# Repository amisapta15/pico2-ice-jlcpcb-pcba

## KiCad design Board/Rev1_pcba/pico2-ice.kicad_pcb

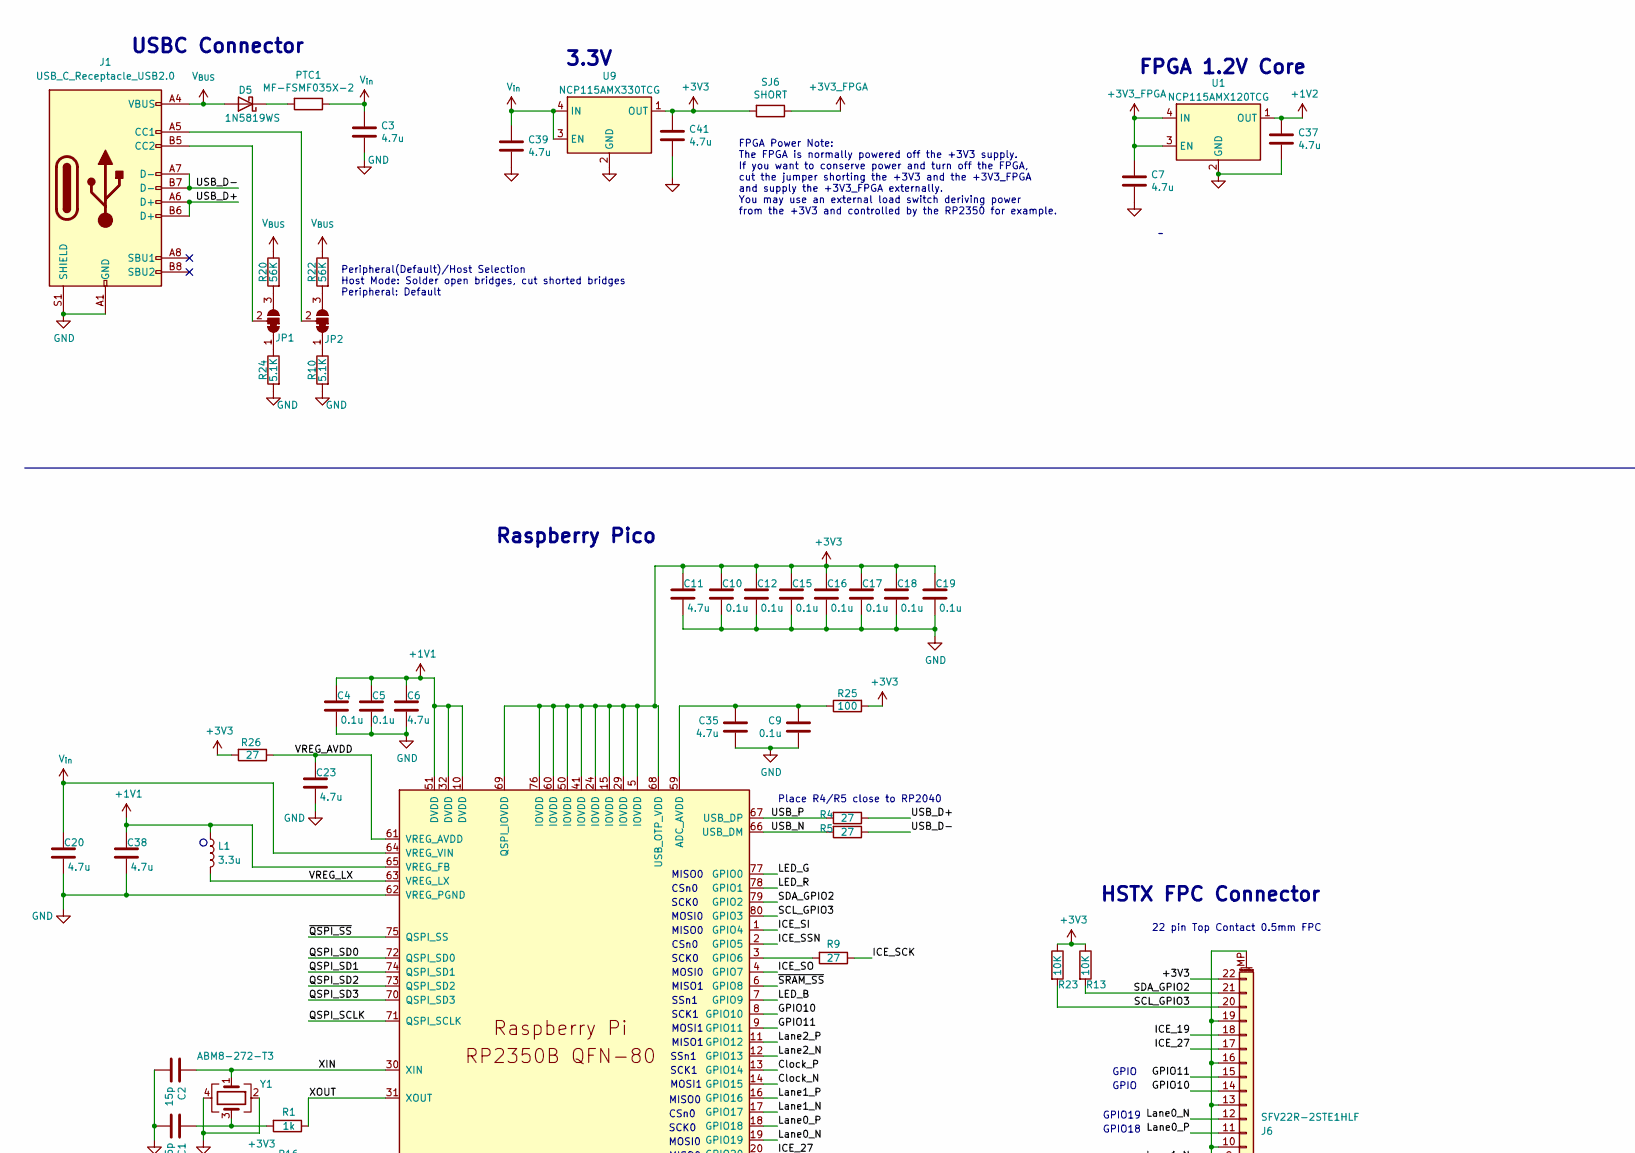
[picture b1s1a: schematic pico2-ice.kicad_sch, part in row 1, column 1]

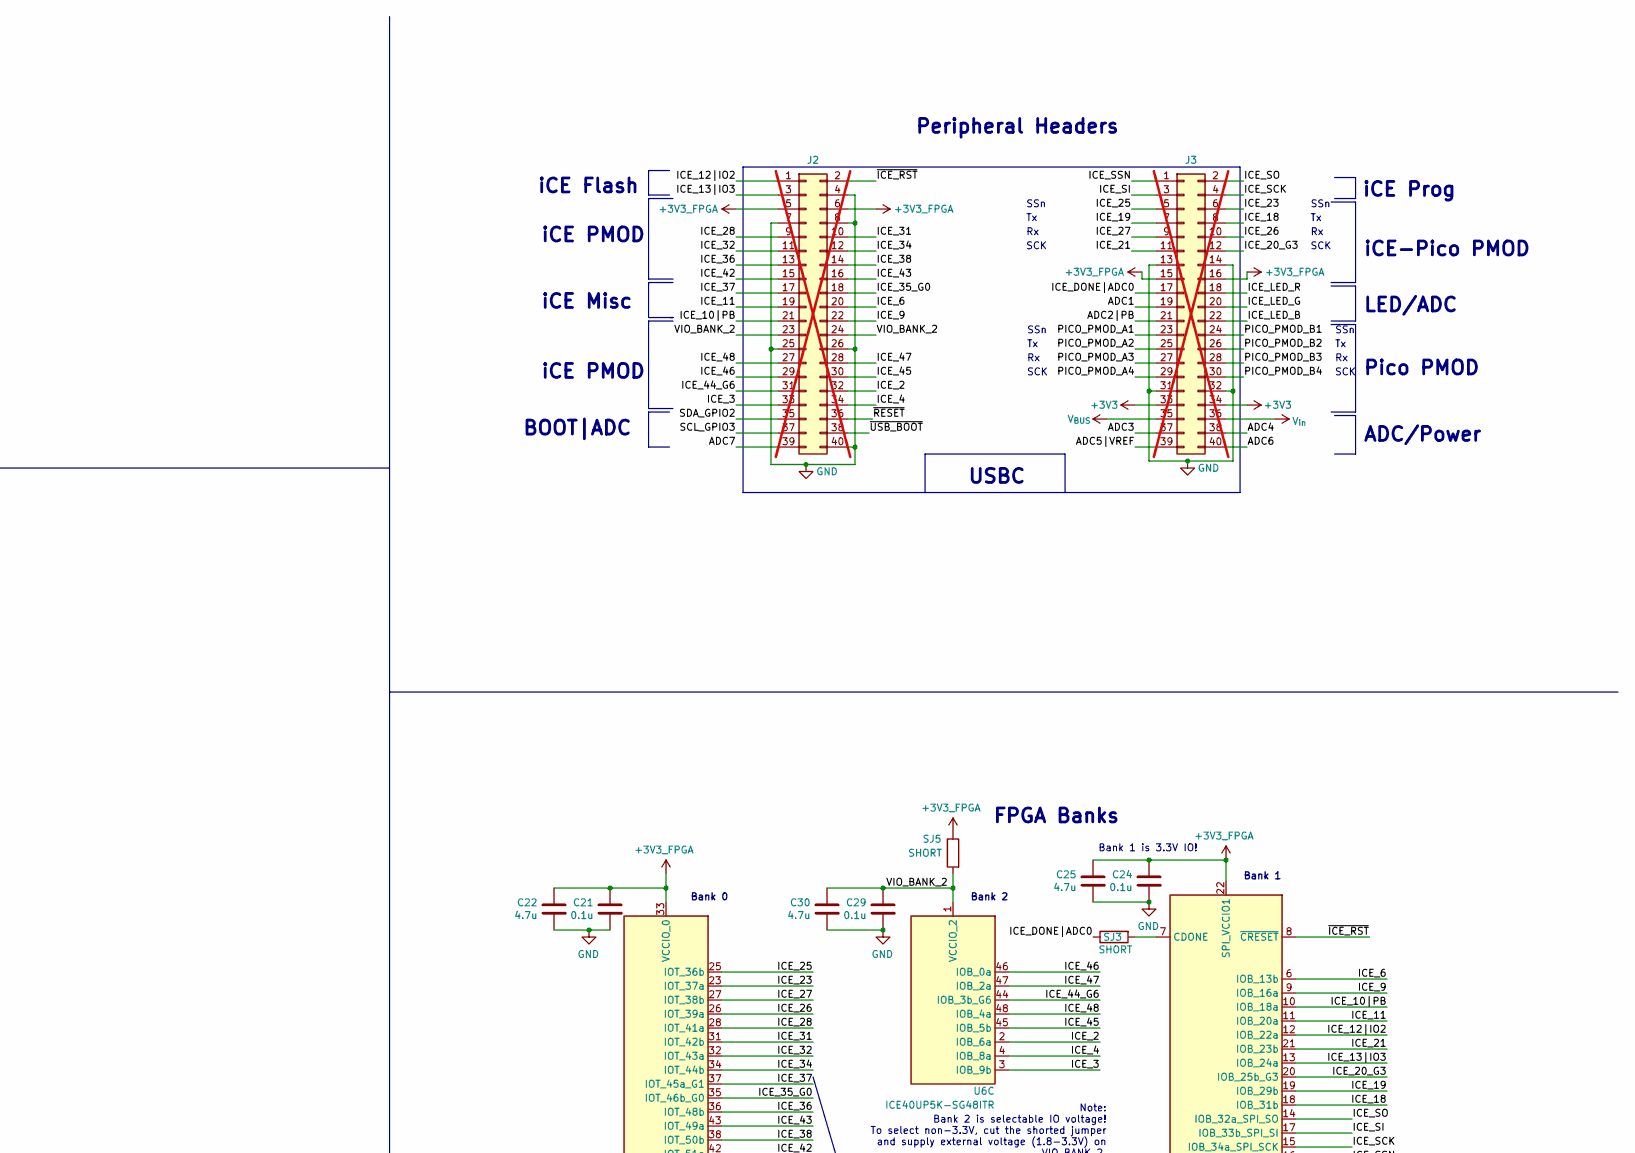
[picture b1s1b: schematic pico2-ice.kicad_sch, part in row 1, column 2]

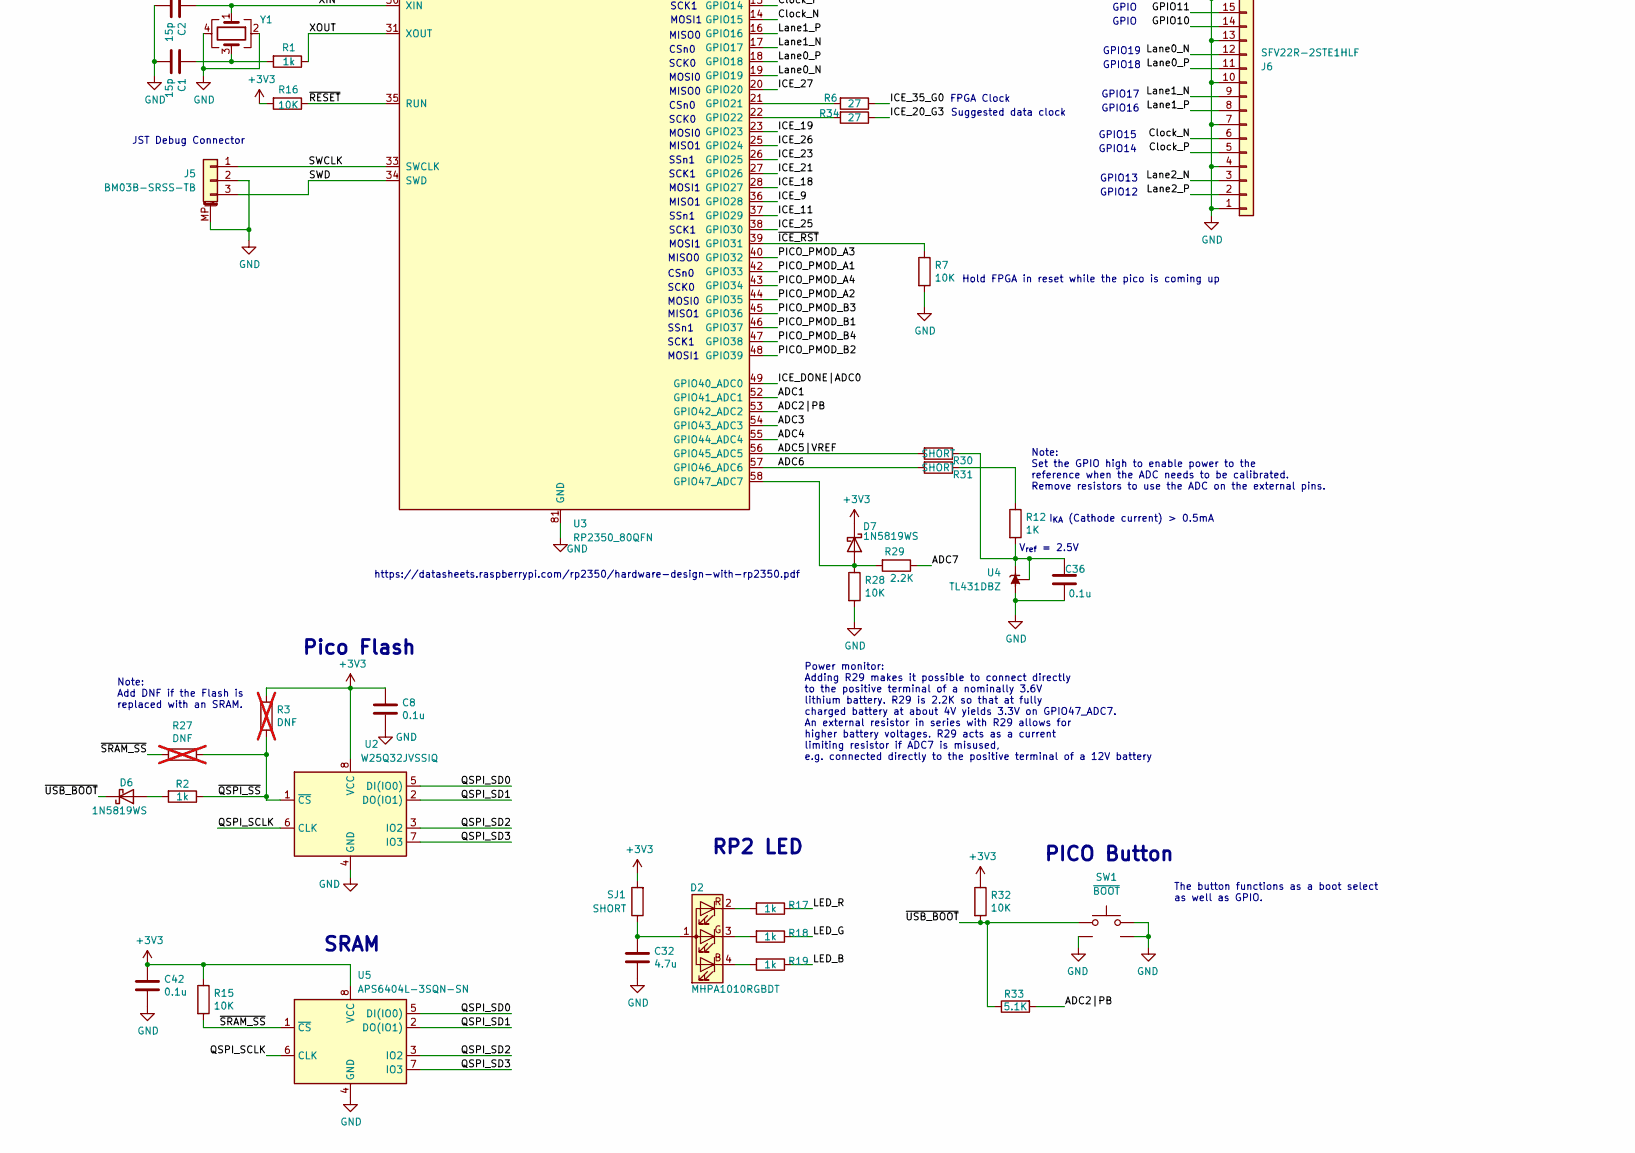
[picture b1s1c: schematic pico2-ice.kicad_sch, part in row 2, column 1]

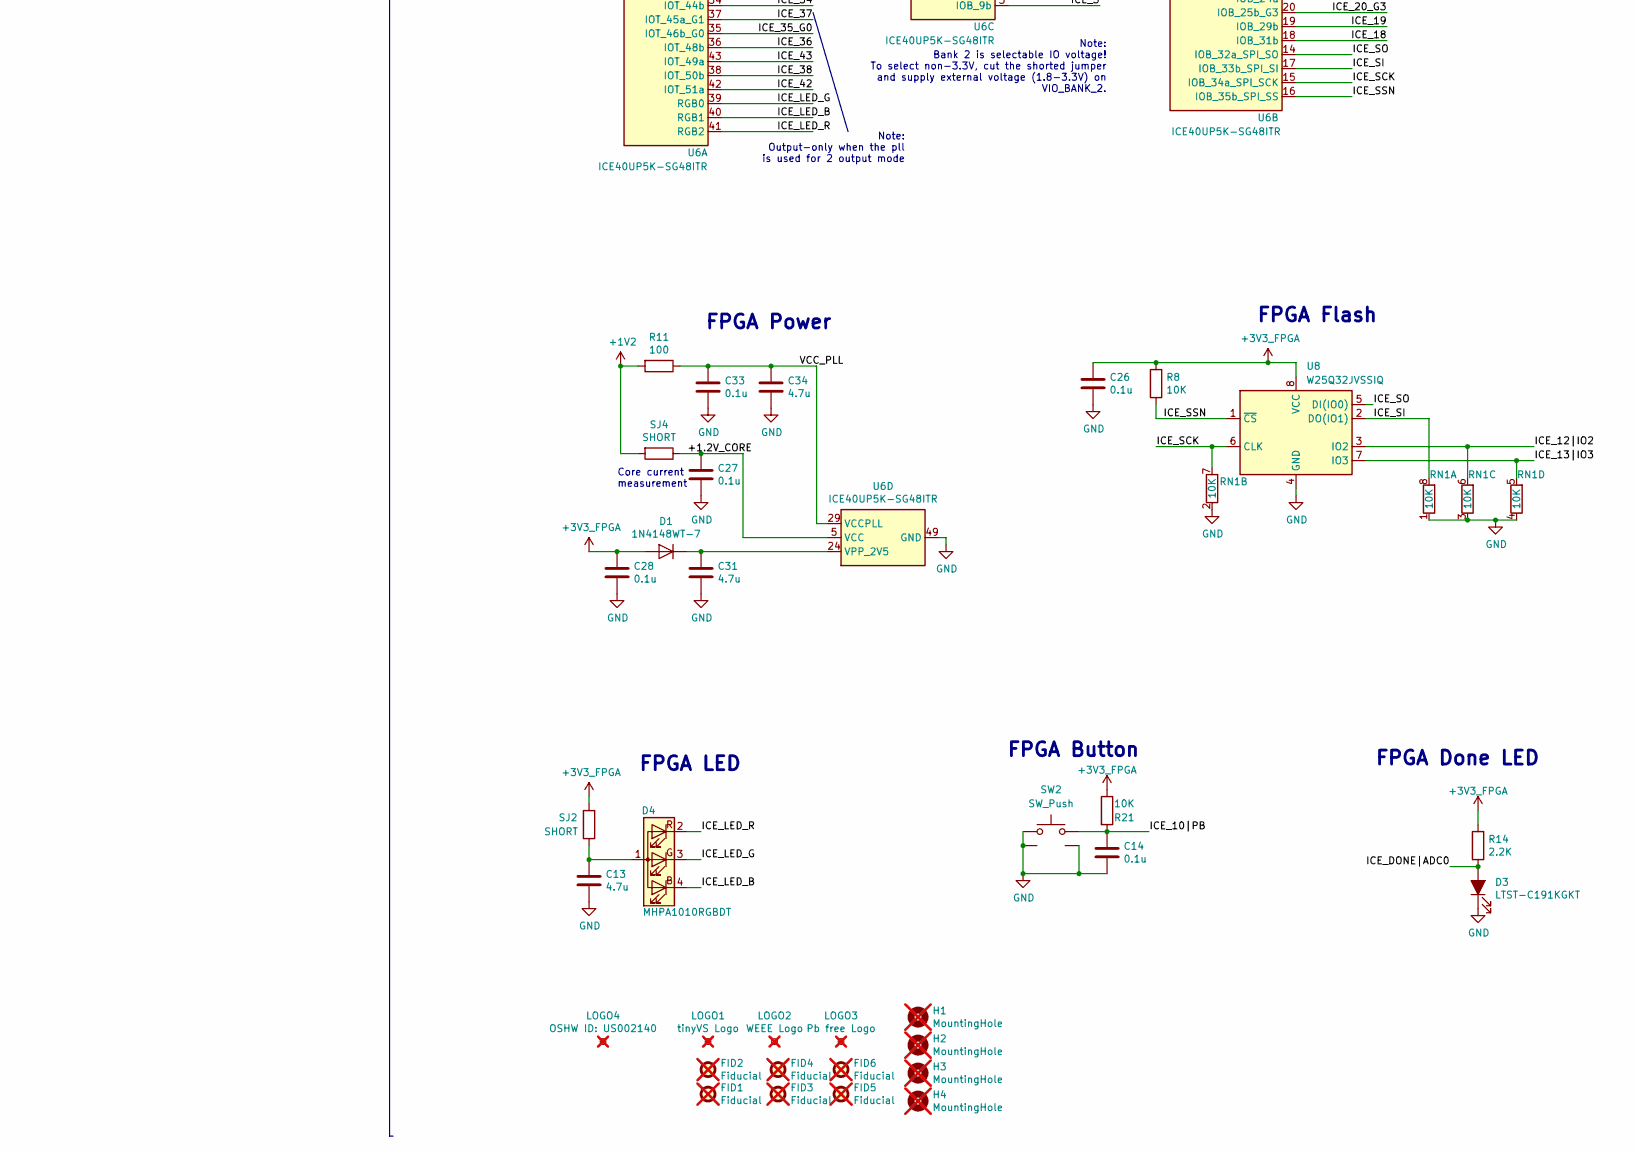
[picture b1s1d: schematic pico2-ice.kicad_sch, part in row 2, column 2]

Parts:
C1, C2: 15p; C_0402_1005Metric; MPN GRM1555C1E150JA01D
C3, C6, C7, C11, C13, C20, C22, C23, C25, C30, C31, C32, C34, C35, C37, C38, C39, C41: 4.7u; C_0402_1005Metric; MPN GRM155R60J475ME87D
C4, C5, C8, C9, C10, C12, C14, C15, C16, C17, C18, C19, C21, C24, C26, C27, C28, C29, C33, C36, C42: 0.1u; C_0402_1005Metric; MPN GRM155R71C104KA88J
D1: 1N4148WT-7; D_SOD-523; MPN 1N4148WT-7
D2, D4: MHPA1010RGBDT; LED_Cree-PLCC4_1x1mm_CW; MPN MHPA1010RGBDT; Digi-Key Part Number LCSC
D3: LTST-C191KGKT; LED_0603_1608Metric; MPN LTST-C191KGKT
D5, D6, D7: 1N5819WS; D_SOD-323; MPN 1N5819WS
FID1, FID2, FID3, FID4, FID5, FID6: Fiducial; Fiducial_0.75mm_Mask1.5mm; MPN DNP; not fitted
H1, H2, H3, H4: MountingHole; MountingHole_2.7mm_M2.5; MPN DNP; not fitted
J1: USB_C_Receptacle_USB2.0; USB_C_Receptacle_HRO_TYPE-C-31-M-12; MPN USB4105-GF-A
J2: Conn_02x20_Odd_Even; PinHeader_2x20_P2.54mm_Vertical_Left; MPN DNP; not fitted
J3: Conn_02x20_Odd_Even; PinHeader_2x20_P2.54mm_Vertical_Right; MPN DNP; not fitted
J5: BM03B-SRSS-TB; JST_SH_BM03B-SRSS-TB_1x03-1MP_P1.00mm_Vertical; MPN BM03B-SRSS-TB
J6: SFV22R-2STE1HLF; AMPHENOL_SFV22R-2STE1HLF; MPN SFV22R-2STE1HLF
JP1, JP2: SolderJumper_3_Bridged12; SolderJumper-3_P1.3mm_Bridged12_RoundedPad1.0x1.5mm
L1: 3.3u; L_pol_2016; MPN MLP2016H3R3MT0S1
LOGO1: tinyVS Logo; tinyAI_logo; MPN DNP; Digi-Key_PN DNP; not fitted
LOGO2: WEEE Logo; WEEE logo; MPN DNP; Digi-Key_PN DNP; not fitted
LOGO3: Pb free Logo; Pb free logo; MPN DNP; Digi-Key_PN DNP; not fitted
LOGO4: OSHW ID: US002140; OSHW_Dual_0.1_Scale_2140; MPN DNP; Digi-Key_PN DNP; not fitted
PTC1: MF-FSMF035X-2; R_0603_1608Metric; MPN MF-FSMF035X-2
R1, R2, R17, R18, R19: 1k; R_0402_1005Metric; MPN RC0402FR-071KL
R3, R27: DNF; R_0402_1005Metric; not fitted
R4, R5, R6, R9, R26, R34: 27; R_0402_1005Metric; MPN RC0402FR-0727RL
R7, R13, R15, R23, R28, R32: 10K; R_0402_1005Metric
R8, R16, R21: 10K; R_0402_1005Metric; MPN RC0402FR-0710KL
R10, R24, R33: 5.1K; R_0402_1005Metric; MPN RC0402FR-075K1L
R11, R25: 100; R_0402_1005Metric; MPN RC0402FR-07100RL
R12: 1K; R_0402_1005Metric; MPN RC0402FR-071KL
R14: 2.2K; R_0402_1005Metric; MPN RC0402FR-072K2L
R20, R22: 56K; R_0402_1005Metric; MPN RC0402FR-0756KL
R29: 2.2K; R_0402_1005Metric
R30, R31: SHORT; SolderJumper-2_P1.3mm_Bridged_RoundedPad1.0x1.5mm; MPN DNP
RN1: 10K; R_Array_Concave_4x0402; MPN YC124-FR-0710KL
SJ1, SJ2, SJ3, SJ4, SJ5, SJ6: SHORT; SolderJumper-2_P1.3mm_Bridged_RoundedPad1.0x1.5mm; MPN DNP
SW1, SW2: CS1213AGF260; PTS820J25KSMTRLFS; MPN CS1213AGF260
U1: NCP115AMX120TCG; OnSemi_XDFN4-1EP_1.0x1.0mm_EP0.52x0.52mm; MPN NCP115AMX120TCG
U2, U8: W25Q32JVSSIQ; SOIC-8_5.23x5.23mm_P1.27mm; MPN W25Q32JVSSIQ
U3: RP2350_80QFN; RP2350B_QFN-80_EP_10.573x10.573_Pitch0.4mm
U4: TL431DBZ; SOT-23
U5: APS6404L-3SQN-SN; SOIC-8_3.9x4.9mm_P1.27mm; MPN APS6404L-3SQN-SN
U6: ICE40UP5K-SG48ITR; QFN-48-1EP_7x7mm_P0.5mm_EP5.6x5.6mm; MPN ICE40UP5K-SG48I
U9: NCP115AMX330TCG; OnSemi_XDFN4-1EP_1.0x1.0mm_EP0.52x0.52mm; MPN NCP115AMX330TCG
Y1: ABM8-272-T3; Crystal_SMD_3225-4Pin_3.2x2.5mm; MPN ABM8-272-T3

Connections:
+1V1: C4.1, C5.1, C6.1, C38.1, L1.1, U3.10 (DVDD), U3.32 (DVDD), U3.51 (DVDD), U3.65 (VREG_FB)
+1V2: C37.1, R11.2, SJ4.2, U1.1 (OUT)
+3V3: C8.1, C10.1, C11.1, C12.1, C15.1, C16.1, C17.1, C18.1, C19.1, C41.1, C42.1, D7.1 (K), J3.33, J3.34, J6.22, R3.1, R13.1, R15.1, R16.2, R23.1, R25.2, R26.2, R32.1, SJ1.2, SJ6.2, U2.8 (VCC), U3.5 (IOVDD), U3.15 (IOVDD), U3.24 (IOVDD), U3.29 (IOVDD), U3.41 (IOVDD), U3.50 (IOVDD), U3.60 (IOVDD), U3.68 (USB_OTP_VDD), U3.69 (QSPI_IOVDD), U3.76 (IOVDD), U5.8 (VCC), U9.1 (OUT)
+3V3_FPGA: C7.1, C21.1, C22.1, C24.1, C25.1, C26.1, C28.1, D1.2 (A), J2.5, J2.6, J3.15, J3.16, R8.2, R14.2, R21.1, SJ2.2, SJ5.1, SJ6.1, U1.3 (EN), U1.4 (IN), U6.22 (SPI_VCCIO1), U6.33 (VCCIO_0), U8.8 (VCC)
/+1.2V_CORE: C27.1, SJ4.1, U6.5 (VCC), U6.30 (VCC)
/ADC1: J3.19, U3.52 (GPIO41_ADC1)
/ADC2|PB: J3.21, R33.2, U3.53 (GPIO42_ADC2)
/ADC3: J3.37, U3.54 (GPIO43_ADC3)
/ADC4: J3.38, U3.55 (GPIO44_ADC4)
/ADC5|VREF: J3.39, R30.2, U3.56 (GPIO45_ADC5)
/ADC6: J3.40, R31.2, U3.57 (GPIO46_ADC6)
/ADC7: J2.39, R29.1
/Clock_N: J6.6, U3.14 (GPIO15)
/Clock_P: J6.5, U3.13 (GPIO14)
/GPIO10: J6.14, U3.8 (GPIO10)
/GPIO11: J6.15, U3.9 (GPIO11)
/ICE_2: J2.32, U6.2 (IOB_6a)
/ICE_3: J2.33, U6.3 (IOB_9b)
/ICE_4: J2.34, U6.4 (IOB_8a)
/ICE_6: J2.20, U6.6 (IOB_13b)
/ICE_9: J2.22, U3.36 (GPIO28), U6.9 (IOB_16a)
/ICE_10|PB: C14.1, J2.21, R21.2, SW2.2, U6.10 (IOB_18a)
/ICE_11: J2.19, U3.37 (GPIO29), U6.11 (IOB_20a)
/ICE_12|IO2: J2.1, RN1.6 (R3.2), U6.12 (IOB_22a), U8.3 (IO2)
/ICE_13|IO3: J2.3, RN1.5 (R4.2), U6.13 (IOB_24a), U8.7 (IO3)
/ICE_18: J3.8, U3.28 (GPIO27), U6.18 (IOB_31b)
/ICE_19: J3.7, J6.18, U3.23 (GPIO23), U6.19 (IOB_29b)
/ICE_20_G3: J3.12, R34.1, U6.20 (IOB_25b_G3)
/ICE_21: J3.11, U3.27 (GPIO26), U6.21 (IOB_23b)
/ICE_23: J3.6, U3.26 (GPIO25), U6.23 (IOT_37a)
/ICE_25: J3.5, U3.38 (GPIO30), U6.25 (IOT_36b)
/ICE_26: J3.10, U3.25 (GPIO24), U6.26 (IOT_39a)
/ICE_27: J3.9, J6.17, U3.20 (GPIO20), U6.27 (IOT_38b)
/ICE_28: J2.9, U6.28 (IOT_41a)
/ICE_31: J2.10, U6.31 (IOT_42b)
/ICE_32: J2.11, U6.32 (IOT_43a)
/ICE_34: J2.12, U6.34 (IOT_44b)
/ICE_35_G0: J2.18, R6.1, U6.35 (IOT_46b_G0)
/ICE_36: J2.13, U6.36 (IOT_48b)
/ICE_37: J2.17, U6.37 (IOT_45a_G1)
/ICE_38: J2.14, U6.38 (IOT_50b)
/ICE_42: J2.15, U6.42 (IOT_51a)
/ICE_43: J2.16, U6.43 (IOT_49a)
/ICE_44_G6: J2.31, U6.44 (IOB_3b_G6)
/ICE_45: J2.30, U6.45 (IOB_5b)
/ICE_46: J2.29, U6.46 (IOB_0a)
/ICE_47: J2.28, U6.47 (IOB_2a)
/ICE_48: J2.27, U6.48 (IOB_4a)
/ICE_DONE|ADC0: D3.2 (A), J3.17, R14.1, SJ3.1, U3.49 (GPIO40_ADC0)
/ICE_LED_B: D4.4 (BK), J3.22, U6.40 (RGB1)
/ICE_LED_G: D4.3 (GK), J3.20, U6.39 (RGB0)
/ICE_LED_R: D4.2 (RK), J3.18, U6.41 (RGB2)
/ICE_SCK: J3.4, R9.1, RN1.7 (R2.2), U6.15 (IOB_34a_SPI_SCK), U8.6 (CLK)
/ICE_SI: J3.3, RN1.8 (R1.2), U3.1 (GPIO4), U6.17 (IOB_33b_SPI_SI), U8.2 (DO(IO1))
/ICE_SO: J3.2, U3.4 (GPIO7), U6.14 (IOB_32a_SPI_SO), U8.5 (DI(IO0))
/ICE_SSN: J3.1, R8.1, U3.2 (GPIO5), U6.16 (IOB_35b_SPI_SS), U8.1 (~CS)
/LED_B: R19.1, U3.7 (GPIO9)
/LED_G: R18.1, U3.77 (GPIO0)
/LED_R: R17.1, U3.78 (GPIO1)
/Lane0_N: J6.12, U3.19 (GPIO19)
/Lane0_P: J6.11, U3.18 (GPIO18)
/Lane1_N: J6.9, U3.17 (GPIO17)
/Lane1_P: J6.8, U3.16 (GPIO16)
/Lane2_N: J6.3, U3.12 (GPIO13)
/Lane2_P: J6.2, U3.11 (GPIO12)
/PICO_PMOD_A1: J3.23, U3.42 (GPIO33)
/PICO_PMOD_A2: J3.25, U3.44 (GPIO35)
/PICO_PMOD_A3: J3.27, U3.40 (GPIO32)
/PICO_PMOD_A4: J3.29, U3.43 (GPIO34)
/PICO_PMOD_B1: J3.24, U3.46 (GPIO37)
/PICO_PMOD_B2: J3.26, U3.48 (GPIO39)
/PICO_PMOD_B3: J3.28, U3.45 (GPIO36)
/PICO_PMOD_B4: J3.30, U3.47 (GPIO38)
/QSPI_SCLK: U2.6 (CLK), U3.71 (QSPI_SCLK), U5.6 (CLK)
/QSPI_SD0: U2.5 (DI(IO0)), U3.72 (QSPI_SD0), U5.5 (DI(IO0))
/QSPI_SD1: U2.2 (DO(IO1)), U3.74 (QSPI_SD1), U5.2 (DO(IO1))
/QSPI_SD2: U2.3 (IO2), U3.73 (QSPI_SD2), U5.3 (IO2)
/QSPI_SD3: U2.7 (IO3), U3.70 (QSPI_SD3), U5.7 (IO3)
/SCL_GPIO3: J2.37, J6.20, R23.2, U3.80 (GPIO3)
/SDA_GPIO2: J2.35, J6.21, R13.2, U3.79 (GPIO2)
/SWCLK: J5.1, U3.33 (SWCLK)
/SWD: J5.3, U3.34 (SWD)
/USB_D+: J1.A6 (D+), J1.B6 (D+), R4.1
/USB_D-: J1.A7 (D-), J1.B7 (D-), R5.1
/USB_N: R5.2, U3.66 (USB_DM)
/USB_P: R4.2, U3.67 (USB_DP)
/VCC_PLL: C33.1, C34.1, R11.1, U6.29 (VCCPLL)
/VIO_BANK_2: C29.1, C30.1, J2.23, J2.24, SJ5.2, U6.1 (VCCIO_2)
/VREG_AVDD: C23.1, R26.1, U3.61 (VREG_AVDD)
/VREG_LX: L1.2, U3.63 (VREG_LX)
/XIN: C2.1, U3.30 (XIN), Y1.1
/XOUT: R1.1, U3.31 (XOUT)
/~ICE_RST: J2.2, R7.1, U3.39 (GPIO31), U6.8 (~CRESET)
/~QSPI_SS: R2.1, R3.2, R27.1, U2.1 (~CS), U3.75 (QSPI_SS)
/~RESET: J2.36, R16.1, U3.35 (RUN)
/~SRAM_SS: R15.2, R27.2, U3.6 (GPIO8), U5.1 (~CS)
/~USB_BOOT: D6.1 (K), J2.38, R32.2, R33.1, SW1.2
GND: C1.2, C2.2, C3.2, C4.2, C5.2, C6.2, C7.2, C8.2, C9.2, C10.2, C11.2, C12.2, C13.2, C14.2, C15.2, C16.2, C17.2, C18.2, C19.2, C20.2, C21.2, C22.2, C23.2, C24.2, C25.2, C26.2, C27.2, C28.2, C29.2, C30.2, C31.2, C32.2, C33.2, C34.2, C35.2, C36.2, C37.2, C38.2, C39.2, C41.2, C42.2, D3.1 (K), J1.A1 (GND), J1.A12 (GND), J1.B1 (GND), J1.B12 (GND), J1.S1 (SHIELD), J2.4, J2.7, J2.8, J2.25, J2.26, J2.40, J3.13, J3.14, J3.31, J3.32, J5.2, J5.MP (MountPin), J6.1, J6.4, J6.7, J6.10, J6.13, J6.16, J6.19, J6.MP (MountPin), R7.2, R10.2, R24.2, R28.2, RN1.1 (R1.1), RN1.2 (R2.1), RN1.3 (R3.1), RN1.4 (R4.1), SW1.1, SW1.SH1, SW1.SH2, SW2.1, SW2.SH1, SW2.SH2, U1.2 (GND), U1.5 (GND), U2.4 (GND), U3.62 (VREG_PGND), U3.81 (GND), U4.3 (A), U5.4 (GND), U6.49 (GND), U8.4 (GND), U9.2 (GND), U9.5 (GND), Y1.2, Y1.4
unnamed: C1.1, R1.2, Y1.3
unnamed: C31.1, D1.1 (K), U6.24 (VPP_2V5)
unnamed: C32.1, D2.1 (A), SJ1.1
unnamed: D2.4 (BK), R19.2
unnamed: D2.3 (GK), R18.2
unnamed: D2.2 (RK), R17.2
unnamed: C13.1, D4.1 (A), SJ2.1
unnamed: D5.1 (K), PTC1.2
unnamed: D6.2 (A), R2.2
unnamed: D7.2 (A), R28.1, R29.2, U3.58 (GPIO47_ADC7)
unnamed: J1.A5 (CC1), JP2.2 (C)
unnamed: J1.B5 (CC2), JP1.2 (C)
unnamed: JP1.1 (A), R24.1
unnamed: JP1.3 (B), R20.2
unnamed: JP2.1 (A), R10.1
unnamed: JP2.3 (B), R22.2
unnamed: R12.1, R31.1
unnamed: C9.1, C35.1, R25.1, U3.59 (ADC_AVDD)
unnamed: R9.2, U3.3 (GPIO6)
unnamed: R6.2, U3.21 (GPIO21)
unnamed: R34.2, U3.22 (GPIO22)
unnamed: C36.1, R12.2, R30.1, U4.1 (K), U4.2 (REF)
unnamed: SJ3.2, U6.7 (CDONE)
V_{BUS}: D5.2 (A), J1.A4 (VBUS), J1.A9 (VBUS), J1.B4 (VBUS), J1.B9 (VBUS), J3.35, R20.1, R22.1
V_{in}: C3.1, C20.1, C39.1, J3.36, PTC1.1, U3.64 (VREG_VIN), U9.3 (EN), U9.4 (IN)

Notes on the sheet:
SCK1
MOSI1
FPGA LED
GPIO
SRAM
iCE PMOD
FPGA 1.2V Core
SCK0
Place R4/R5 close to RP2040
GPIO18
Pico PMOD
SSn1
SSn
SCK
Note: Output-only when the pll is used for 2 output mode
GPIO14
MOSI0
HSTX FPC Connector
MISO1
Bank 1 is 3.3V IO!
FPGA Power
Bank 2
https://datasheets.raspberrypi.com/rp2350/hardware-design-with-rp2350.pdf
CSn0
USBC Connector
iCE Misc
GPIO15
MISO0
GPIO17
The button functions as a boot select as well as GPIO.
FPGA Button
Peripheral Headers
LED/ADC
GPIO16
Suggested data clock
RP2 LED
ADC/Power
Note: Bank 2 is selectable IO voltage! To select non-3.3V, cut the shorted jumper and supply external voltage (1.8-3.3V) on VIO_BANK_2.
Note: Set the GPIO high to enable power to the reference when the ADC needs to be calibrated. Remove resistors to use the ADC on the external pins.
JST Debug Connector

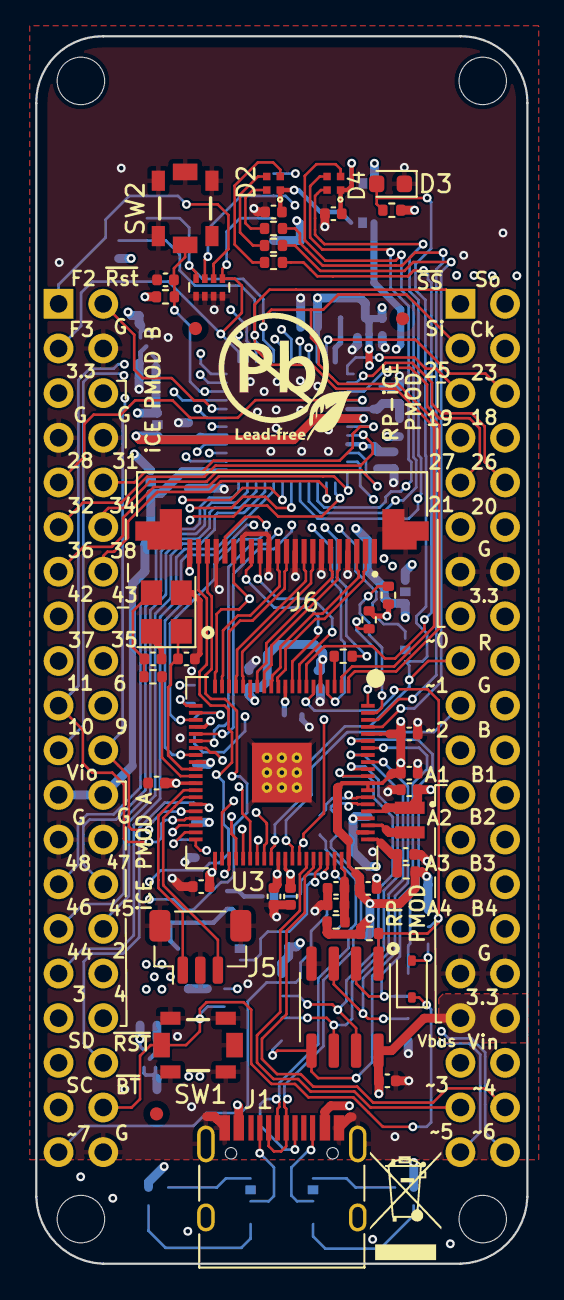
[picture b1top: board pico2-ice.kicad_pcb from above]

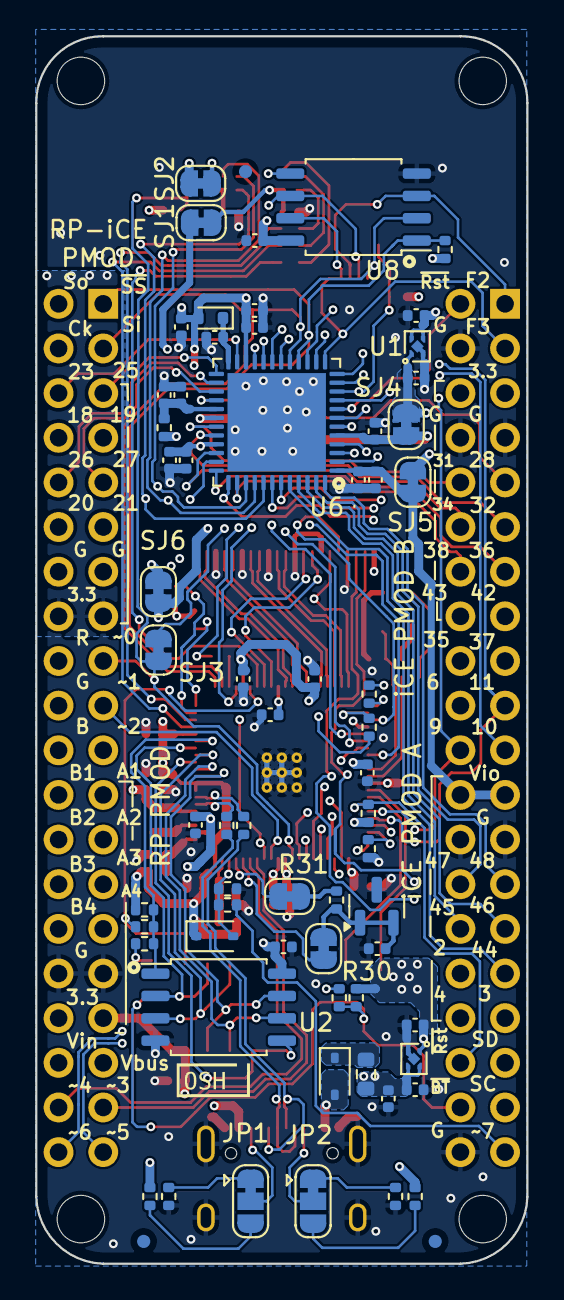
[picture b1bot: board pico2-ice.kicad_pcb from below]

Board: 4 copper layers, 27.9 x 69.8 mm, 123 parts (67 on the bottom side), 123 nets.

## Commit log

2025-04-21 Elongated PCB and remove Fab files
